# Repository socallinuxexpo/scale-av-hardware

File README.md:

# scale-av-hardware
Scale AV Box Hardwares - Descriptions and Design Files

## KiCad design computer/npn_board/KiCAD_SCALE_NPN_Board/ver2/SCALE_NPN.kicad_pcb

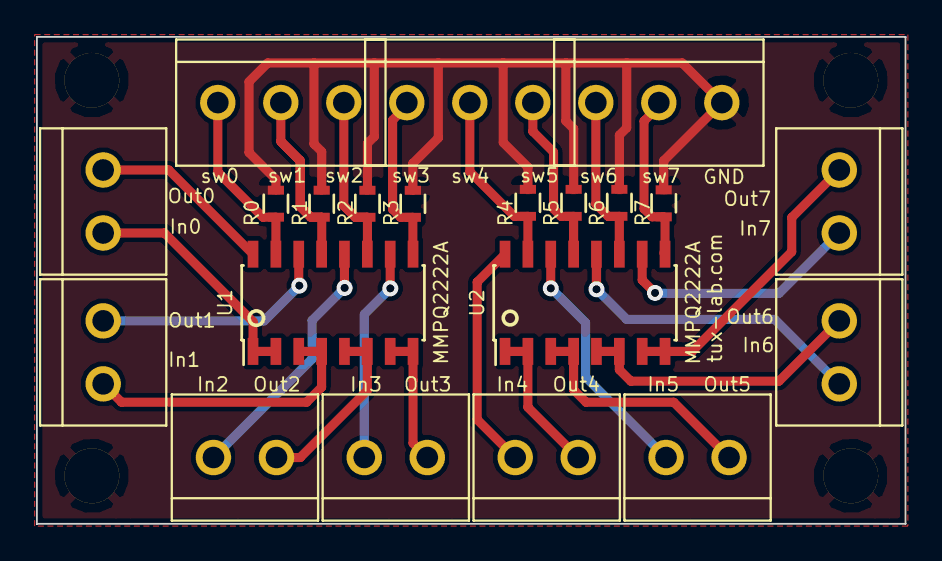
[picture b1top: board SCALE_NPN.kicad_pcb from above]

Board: 2 copper layers, 48.3 x 27.1 mm, 25 parts (0 on the bottom side), 25 nets.

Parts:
MountingHole-4-40, MountingHole-4-40#2, MountingHole-4-40#3, MountingHole-4-40#4: VAL**; MountingHole-4-40
P1, P2, P3, P4, P5, P6, P7, P8: CONN_01X02; TermB_OnShore_3d5mm
P9, P10, P11: CONN_01X03; TermB_OnShore_3POS_3d5mm
R0, R1, R2, R3, R4, R5, R6, R7: R; R_0603
U1, U2: MMPQ2222A; SOIC-16_3.9x9.9mm_Pitch1.27mm

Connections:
/In1: P1.1, U1.1, U1.2
/In2: P2.1, U1.3, U1.4
/In3: P3.1, U1.5, U1.6
/In4: P4.1, U1.7, U1.8
/In5: P5.1, U2.1, U2.2
/In6: P6.1, U2.3, U2.4
/In7: P7.1, U2.5, U2.6
/In8: P8.1, U2.7, U2.8
/Out1: P1.2, U1.16
/Out2: P2.2, U1.14
/Out3: P3.2, U1.12
/Out4: P4.2, U1.10
/Out5: P5.2, U2.16
/Out6: P6.2, U2.14
/Out7: P7.2, U2.12
/Out8: P8.2, U2.10
/SW1: P9.1, R0.1, U1.15
/SW2: P9.2, R1.1, U1.13
/SW3: P9.3, R2.1, U1.11
/SW4: P10.1, R3.1, U1.9
/SW5: P10.2, R4.1, U2.15
/SW6: P10.3, R5.1, U2.13
/SW7: P11.1, R6.1, U2.11
/SW8: P11.2, R7.1, U2.9
GND: P11.3, R0.2, R1.2, R2.2, R3.2, R4.2, R5.2, R6.2, R7.2

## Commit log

2015-12-22 Acrylic Case Laser Cut Patterns (Inkscape) & NPN board layout (KiCAD)
2015-12-22 Import of David's Camera Mount design.
2016-10-05 wiring overview.
    Here is overview of internal wiring of AV box.
2016-10-05 Parts list with sources.
    Parts list for podium computer.
2019-02-05 v1/3mm_acrylic_sheet.svg
2019-02-05 v2 openscad
2019-02-05 move files
2019-02-05 circuit board export
2019-02-06 rework files for export.
2019-02-06 turn the case around.
2019-02-06 docs and make script.
2019-02-06 add .gitignore
2019-02-06 fix typo
2019-02-06 updated scaleav.dxf that openscad like better.
2019-02-12 Tweek settings tab/slot sizes.
2019-02-12 tweeks after first printing.
2019-02-13 more tweaks.
2019-02-14 hopefully final tweeks made after first cutting.
2019-09-24 more fixes.
2019-09-24 move things around.
2019-10-12 remove unused file.
2019-10-12 updated rendering
2019-10-12 allow side to be passed
2019-10-12 make it so bottom panel can not be installed upside down.
2019-10-12 rework panels so fronts can be cut on one sheet.
2019-10-18 update image url.
2019-10-30 adding alignment_tool jig
2019-12-07 working on alignment tool.
2022-08-15 first pass at mount for prisual camera
